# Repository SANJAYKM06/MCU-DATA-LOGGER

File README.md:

# MCU-DATA-LOGGER
The MCU Data Logger is designed to log data from various sensors or peripherals connected to an ATmega328-AU microcontroller.

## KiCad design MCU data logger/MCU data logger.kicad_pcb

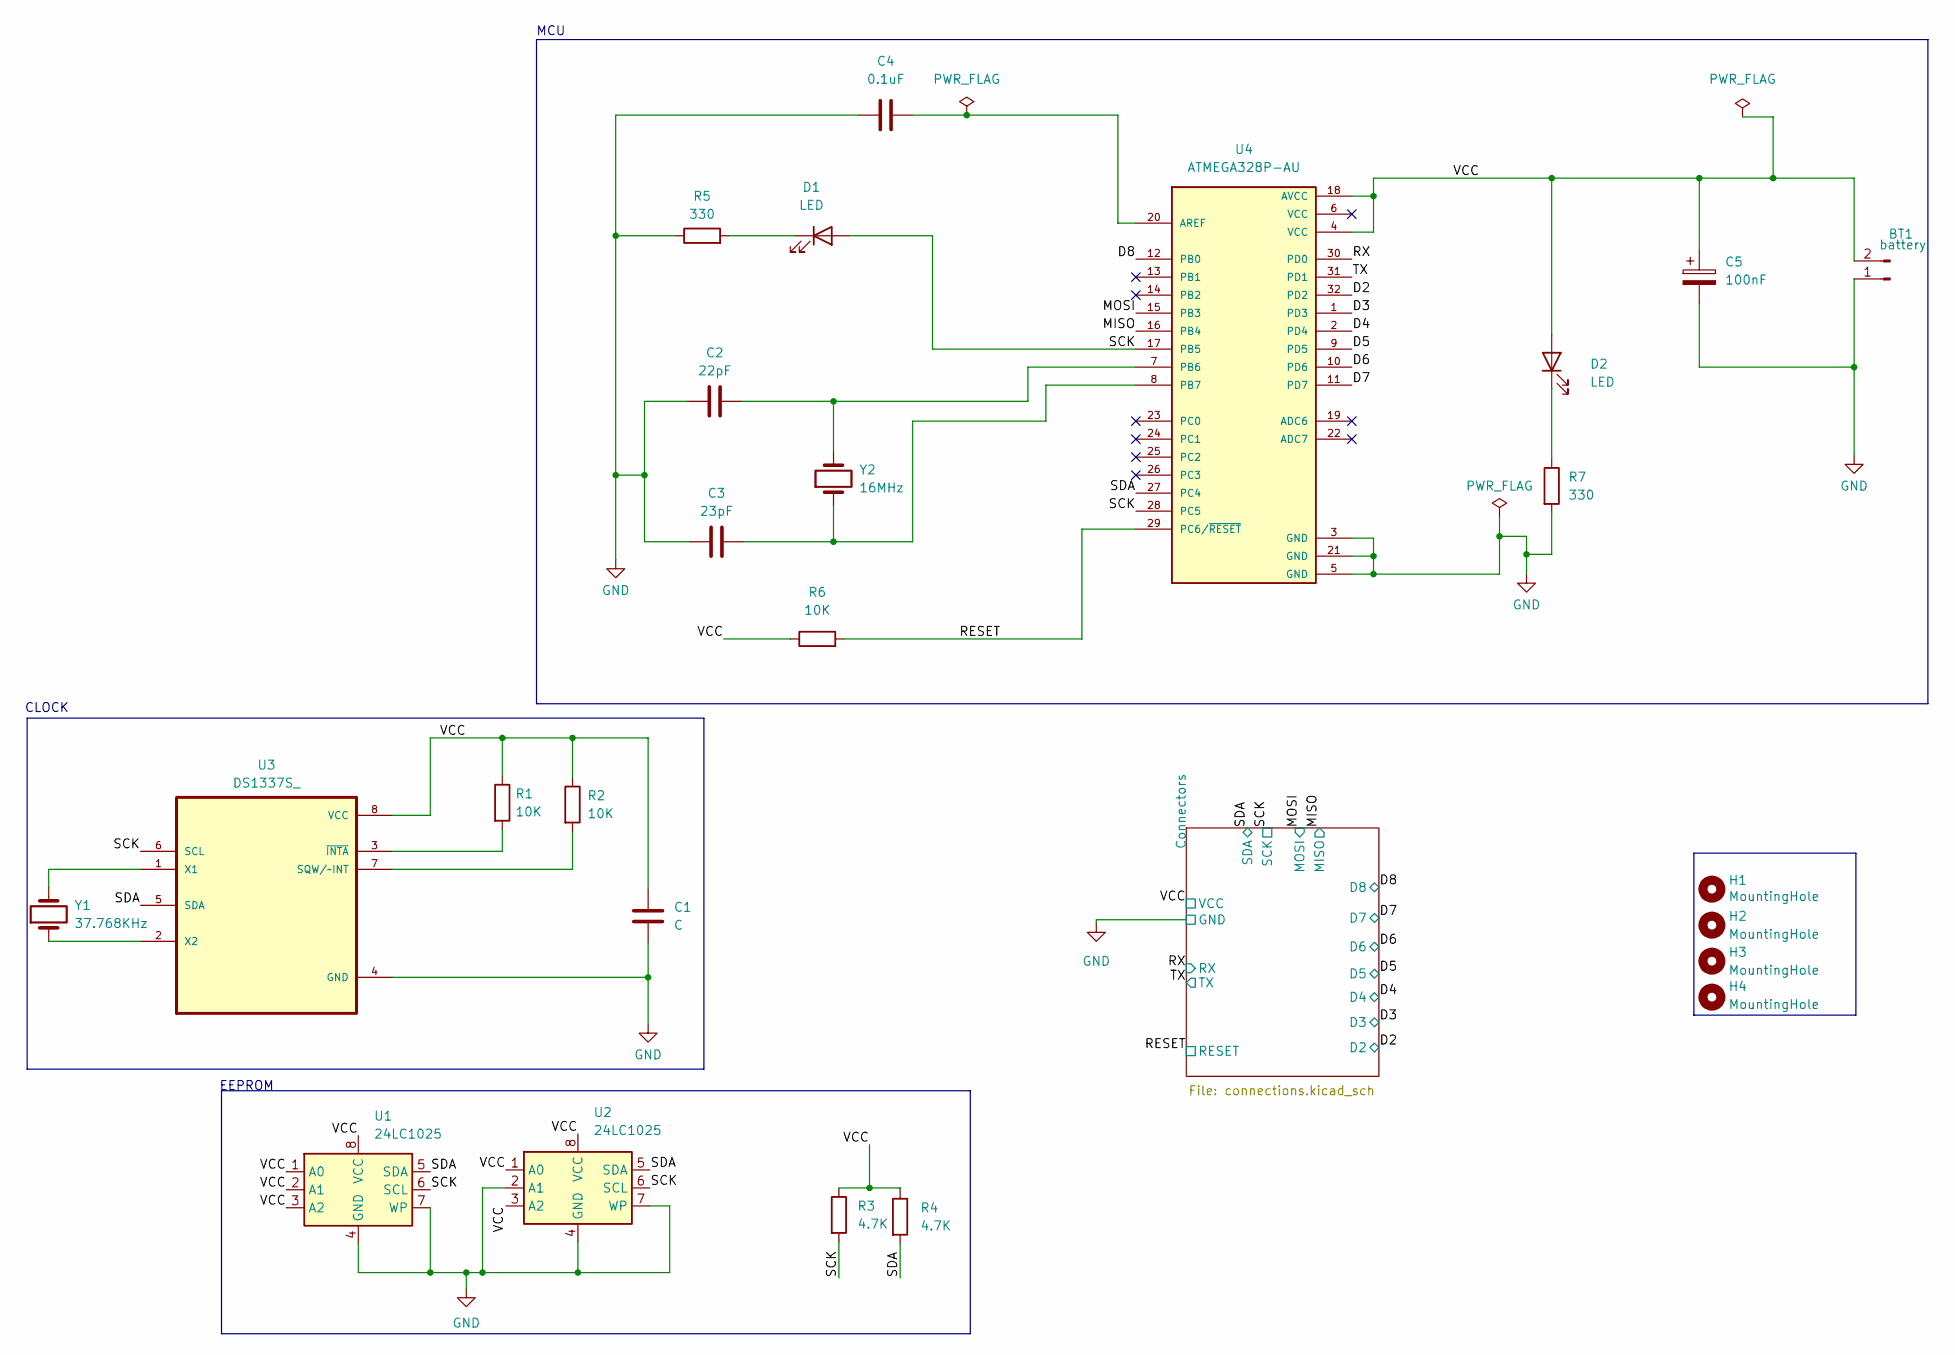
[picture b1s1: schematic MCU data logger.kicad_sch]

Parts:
BT1: battery; PinHeader_1x02_P2.54mm_Vertical
C1: C; C_0805_2012Metric
C2: 22pF; C_0805_2012Metric
C3: 23pF; C_0805_2012Metric
C4: 0.1uF; C_0805_2012Metric
C5: 100nF; C_0805_2012Metric
D1, D2: LED; LED_0805_2012Metric
H1, H2, H3, H4: MountingHole; MountingHole_2.1mm
R1, R2, R6: 10K; R_0805_2012Metric
R3, R4: 4.7K; R_0805_2012Metric
R5, R7: 330; R_0805_2012Metric
U1, U2: 24LC1025; SOIC-8_5.3x5.3mm_P1.27mm
U3: DS1337S_; DS1337S
U4: ATMEGA328P-AU; QFP80P900X900X120-32N
Y1: 37.768KHz; Crystal_SMD_5032-2Pin_5.0x3.2mm_HandSoldering
Y2: 16MHz; Crystal_SMD_5032-2Pin_5.0x3.2mm_HandSoldering

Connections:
/D2: U4.32 (PD2); also elsewhere on the board
/D3: U4.1 (PD3); also elsewhere on the board
/D4: U4.2 (PD4); also elsewhere on the board
/D5: U4.9 (PD5); also elsewhere on the board
/D6: U4.10 (PD6); also elsewhere on the board
/D7: U4.11 (PD7); also elsewhere on the board
/D8: U4.12 (PB0); also elsewhere on the board
/MISO: U4.16 (PB4); also elsewhere on the board
/MOSI: U4.15 (PB3); also elsewhere on the board
/RESET: R6.2, U4.29 (PC6/~RESET); also elsewhere on the board
/RX: U4.30 (PD0); also elsewhere on the board
/SCK: D1.2 (A), R3.2, U1.6 (SCL), U2.6 (SCL), U3.6 (SCL), U4.17 (PB5), U4.28 (PC5); also elsewhere on the board
/SDA: R4.2, U1.5 (SDA), U2.5 (SDA), U3.5 (SDA), U4.27 (PC4); also elsewhere on the board
/TX: U4.31 (PD1); also elsewhere on the board
/VCC: BT1.2, C1.1, C5.1, D2.2 (A), R1.1, R2.1, R3.1, R4.1, R6.1, U1.1 (A0), U1.2 (A1), U1.3 (A2), U1.8 (VCC), U2.1 (A0), U2.3 (A2), U2.8 (VCC), U3.8 (VCC), U4.4 (VCC), U4.18 (AVCC); also elsewhere on the board
GND: BT1.1, C1.2, C2.1, C3.1, C4.1, C5.2, R5.1, R7.2, U1.4 (GND), U1.7 (WP), U2.2 (A1), U2.4 (GND), U2.7 (WP), U3.4 (GND), U4.3 (GND), U4.5 (GND), U4.21 (GND); also elsewhere on the board
unnamed: D1.1 (K), R5.2
unnamed: D2.1 (K), R7.1
unnamed: R2.2, U3.7 (SQW/~INT)
unnamed: U3.1 (X1), Y1.2
unnamed: U3.2 (X2), Y1.1
unnamed: R1.2, U3.3 (~INTA)
unnamed: C4.2, U4.20 (AREF)
unnamed: C2.2, U4.7 (PB6), Y2.2
unnamed: C3.2, U4.8 (PB7), Y2.1

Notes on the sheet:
EEPROM
CLOCK
MCU

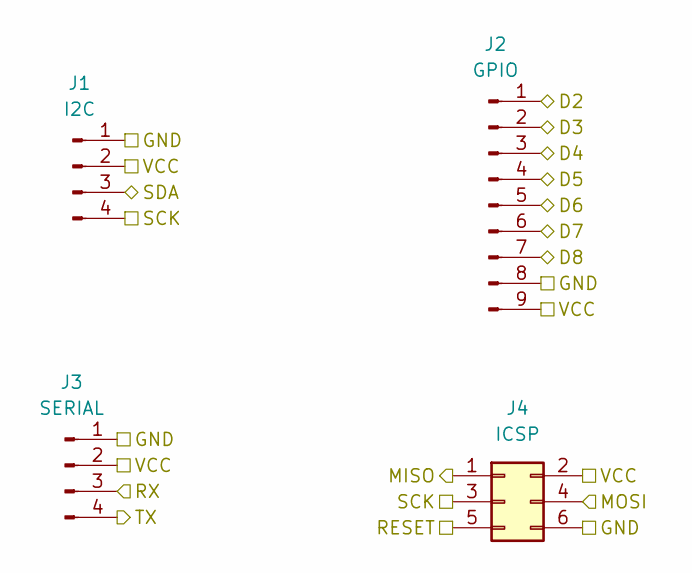
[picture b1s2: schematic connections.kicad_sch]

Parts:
J1: I2C; PinHeader_1x04_P2.54mm_Vertical
J2: GPIO; PinSocket_1x09_P2.54mm_Vertical
J3: SERIAL; PinHeader_1x04_P2.54mm_Vertical
J4: ICSP; PinHeader_2x03_P2.54mm_Vertical

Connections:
/D2: J2.1; also elsewhere on the board
/D3: J2.2; also elsewhere on the board
/D4: J2.3; also elsewhere on the board
/D5: J2.4; also elsewhere on the board
/D6: J2.5; also elsewhere on the board
/D7: J2.6; also elsewhere on the board
/D8: J2.7; also elsewhere on the board
/MISO: J4.1; also elsewhere on the board
/MOSI: J4.4; also elsewhere on the board
/RESET: J4.5; also elsewhere on the board
/RX: J3.3; also elsewhere on the board
/SCK: J1.4, J4.3; also elsewhere on the board
/SDA: J1.3; also elsewhere on the board
/TX: J3.4; also elsewhere on the board
/VCC: J1.2, J2.9, J3.2, J4.2; also elsewhere on the board
GND: J1.1, J2.8, J3.1, J4.6; also elsewhere on the board

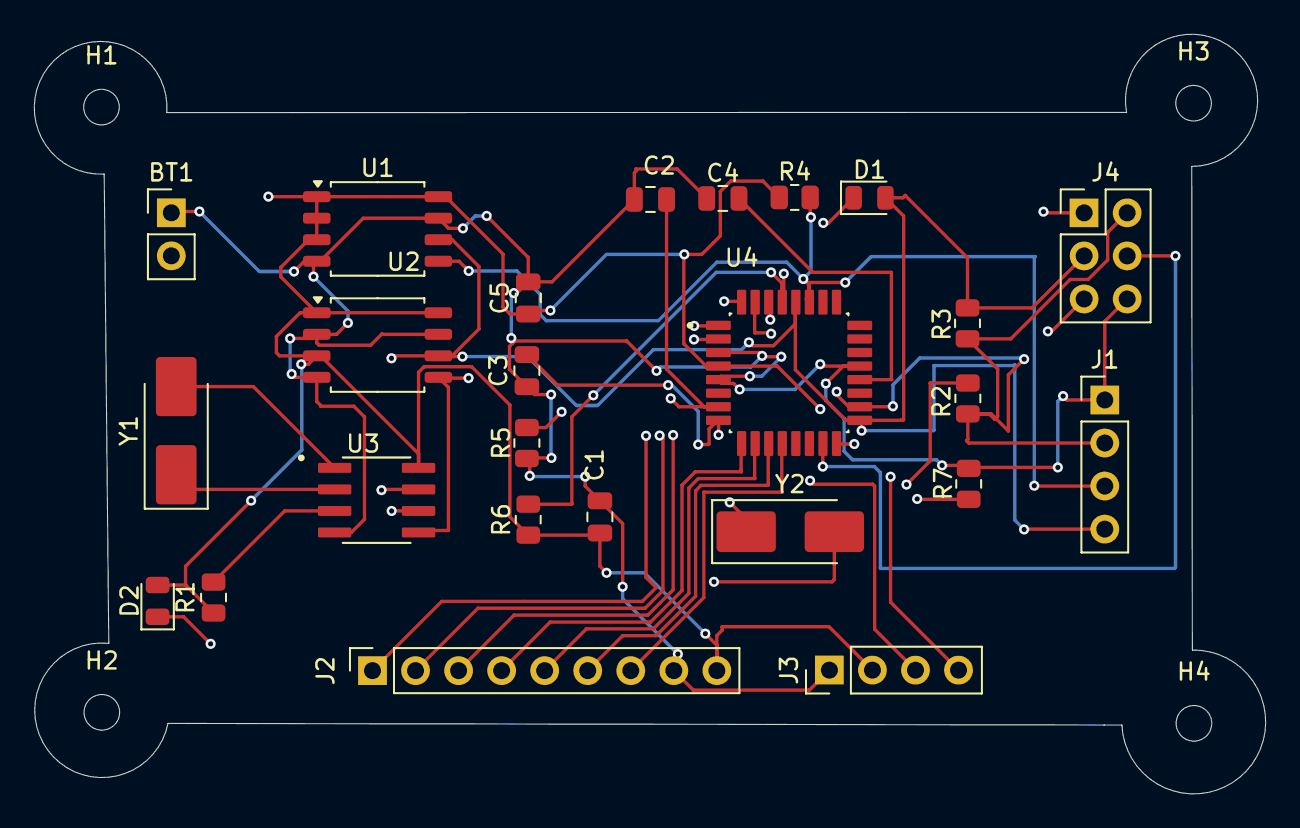
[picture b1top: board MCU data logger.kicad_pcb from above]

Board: 4 copper layers, 72.7 x 44.8 mm, 29 parts (0 on the bottom side), 25 nets.
